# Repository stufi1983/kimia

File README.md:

# kimia
Digital heater for chemical reaction

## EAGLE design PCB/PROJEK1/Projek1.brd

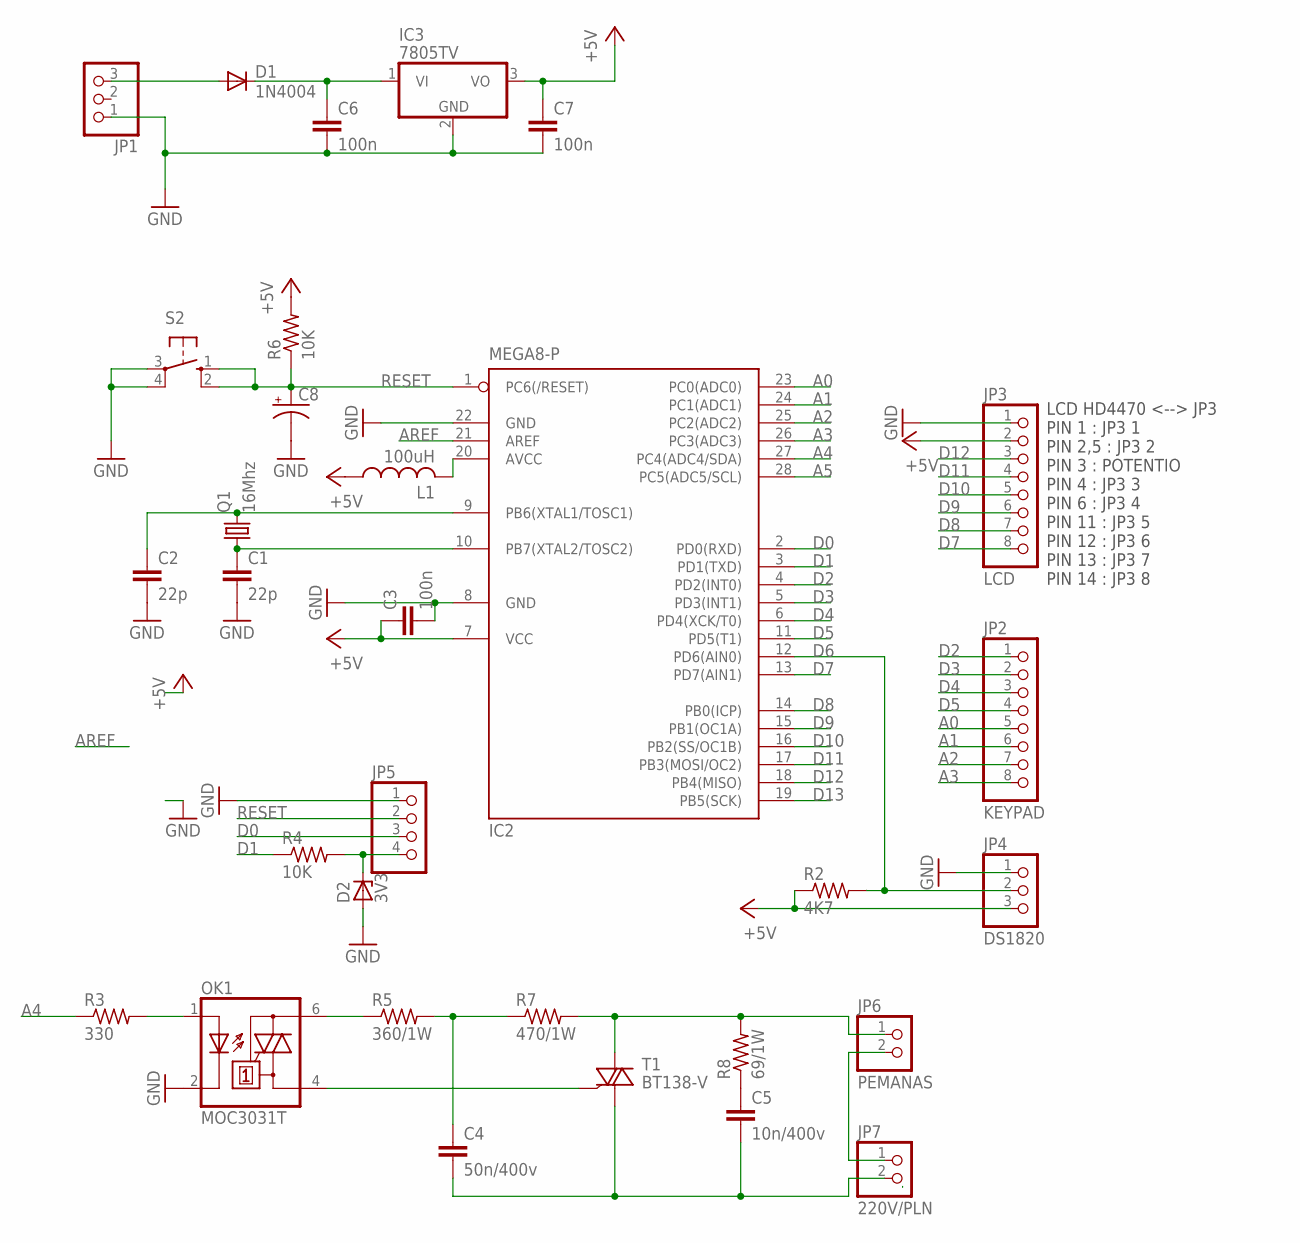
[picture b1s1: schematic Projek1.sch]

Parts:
C1, C2: 22p; C025-025X050
C3, C6, C7: 100n; C050-025X075
C4: 50n/400v; C150-064X183
C5: 10n/400v; C150-064X183
C8: CPOL-USE2-5; E2-5
D1: 1N4004; DO41-10
D2: 3V3; DO35Z10
IC2: MEGA8-P; DIL28-3
IC3: 7805TV; TO220V
JP1: PINHD-1X3; 1X03
JP2: KEYPAD; 1X08
JP3: LCD; 1X08
JP4: DS1820; 1X03
JP5: PINHD-1X4; 1X04
JP6: PEMANAS; 1X02
JP7: 220V/PLN; 1X02
L1: 100uH; 0207/10
OK1: MOC3031T; DIL06B
Q1: 16Mhz; HC49U70
R2: 4K7; 0309/10
R3: 330; 0309/10
R4, R6: 10K; 0309/10
R5: 360/1W; 0414/15
R7: 470/1W; 0414/15
R8: 69/1W; 0414/15
S2: 10-XX; B3F-10XX
T1: BT138-V; TO220BV

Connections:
+5V: C3.1, C7.1, IC2.7 (VCC), IC3.3 (VO), JP3.2, JP4.3, L1.1, R2.1, R6.2
A0: IC2.23 (PC0(ADC0)), JP2.5
A1: IC2.24 (PC1(ADC1)), JP2.6
A2: IC2.25 (PC2(ADC2)), JP2.7
A3: IC2.26 (PC3(ADC3)), JP2.8
A4: IC2.27 (PC4(ADC4/SDA)), R3.1
A5: IC2.28 (PC5(ADC5/SCL))
AREF: IC2.21 (AREF)
D0: IC2.2 (PD0(RXD)), JP5.3
D1: IC2.3 (PD1(TXD)), R4.1
D2: IC2.4 (PD2(INT0)), JP2.1
D3: IC2.5 (PD3(INT1)), JP2.2
D4: IC2.6 (PD4(XCK/T0)), JP2.3
D5: IC2.11 (PD5(T1)), JP2.4
D6: IC2.12 (PD6(AIN0)), JP4.2, R2.2
D7: IC2.13 (PD7(AIN1)), JP3.8
D8: IC2.14 (PB0(ICP)), JP3.7
D9: IC2.15 (PB1(OC1A)), JP3.6
D10: IC2.16 (PB2(SS/OC1B)), JP3.5
D11: IC2.17 (PB3(MOSI/OC2)), JP3.4
D12: IC2.18 (PB4(MISO)), JP3.3
D13: IC2.19 (PB5(SCK))
GND: C1.2, C2.2, C3.2, C6.2, C7.2, C8.-, D2.A, IC2.8 (GND), IC2.22 (GND), IC3.2 (GND), JP1.1, JP3.1, JP4.1, JP5.1, OK1.2 (C), S2.3, S2.4 (P1)
unnamed: D1.A, JP1.3
unnamed: C2.1, IC2.9 (PB6(XTAL1/TOSC1)), Q1.2
unnamed: C1.1, IC2.10 (PB7(XTAL2/TOSC2)), Q1.1
unnamed: C6.1, D1.C, IC3.1 (VI)
unnamed: IC2.20 (AVCC), L1.2
unnamed: OK1.1 (A), R3.2
unnamed: D2.C, JP5.4, R4.2
unnamed: OK1.4 (A1), T1.G
unnamed: JP6.1, R7.2, R8.2, T1.T2 (A2)
unnamed: OK1.6 (A2), R5.1
unnamed: C4.1, R5.2, R7.1
unnamed: C4.2, C5.2, JP7.2, T1.T1 (A1)
unnamed: C5.1, R8.1
unnamed: JP6.2, JP7.1
RESET: C8.+, IC2.1 (PC6(/RESET)), JP5.2, R6.1, S2.1 (S), S2.2 (S1)

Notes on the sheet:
LCD HD4470 <--> JP3 PIN 1 : JP3 1 PIN 2,5 : JP3 2 PIN 3 : POTENTIO PIN 4 : JP3 3 PIN 6 : JP3 4 PIN 11 : JP3 5 PIN 12 : JP3 6 PIN 13 : JP3 7 PIN 14 : JP3 8

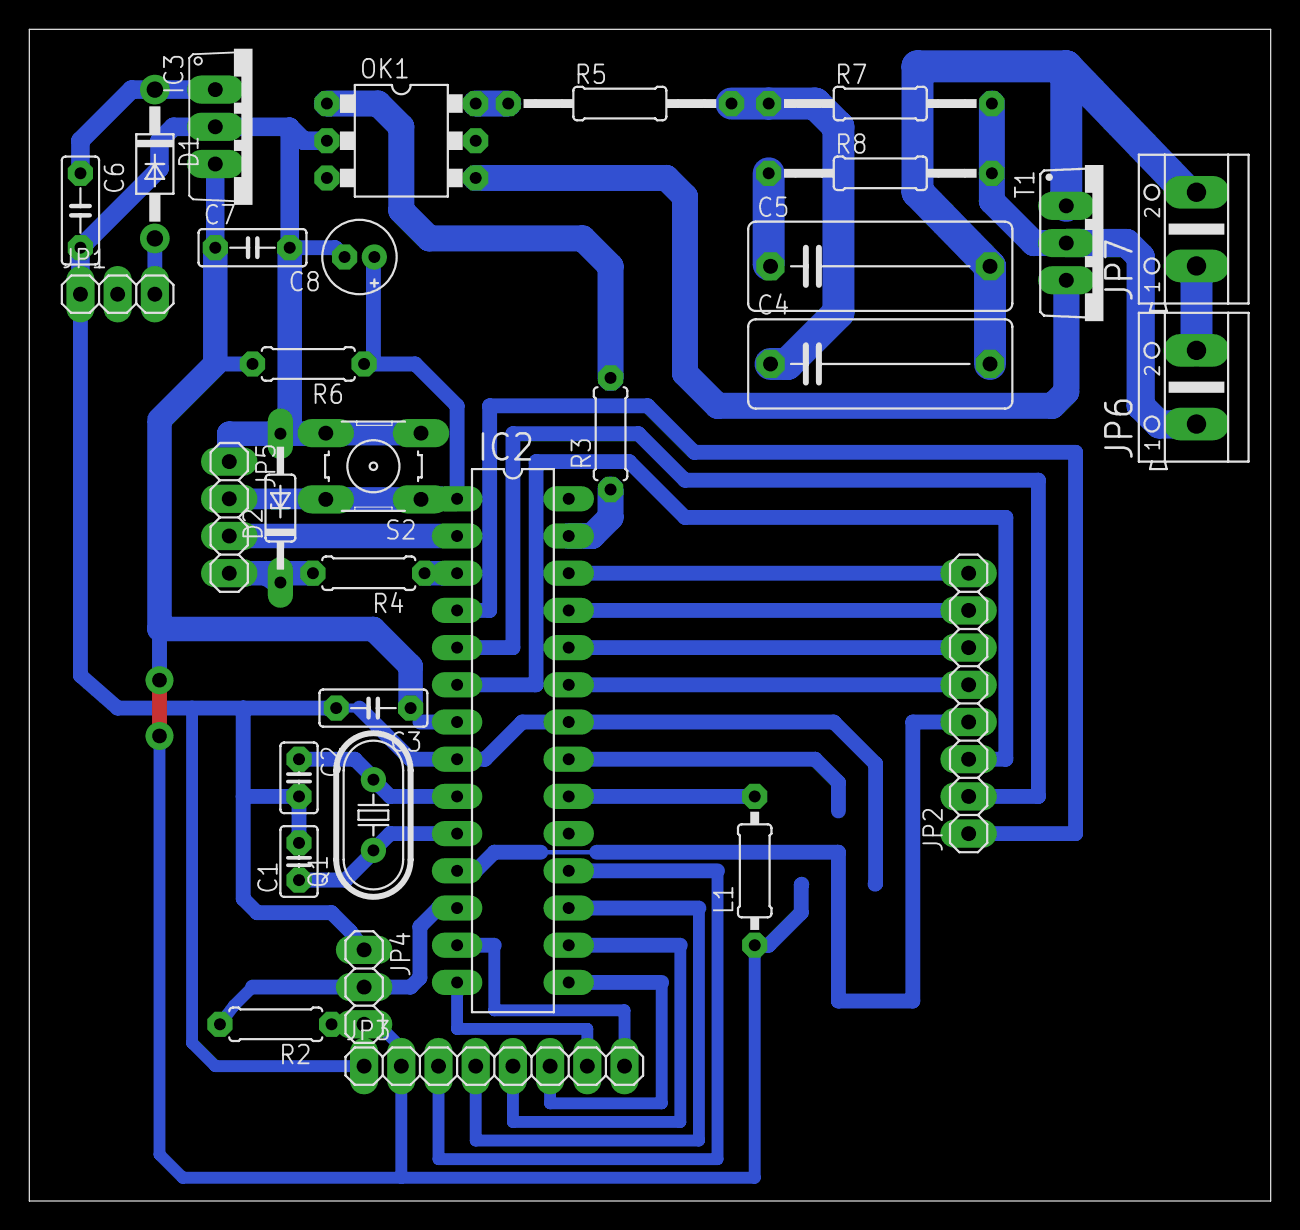
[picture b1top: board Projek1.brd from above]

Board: 2 copper layers, 84.8 x 80.0 mm, 31 parts (0 on the bottom side), 35 nets.

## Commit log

2015-06-05 Added board and firmware
2015-06-05 Create readme
    for user
2016-08-22 Issue: add MAX6675 reading
    Add: MAX6675 reading
    Fix:
    Doc:
    Sty:
    ToDo: uncomment for max, make choices
    Test:
2017-05-28 VRValue double
2022-08-22 Add Pengering gabah
